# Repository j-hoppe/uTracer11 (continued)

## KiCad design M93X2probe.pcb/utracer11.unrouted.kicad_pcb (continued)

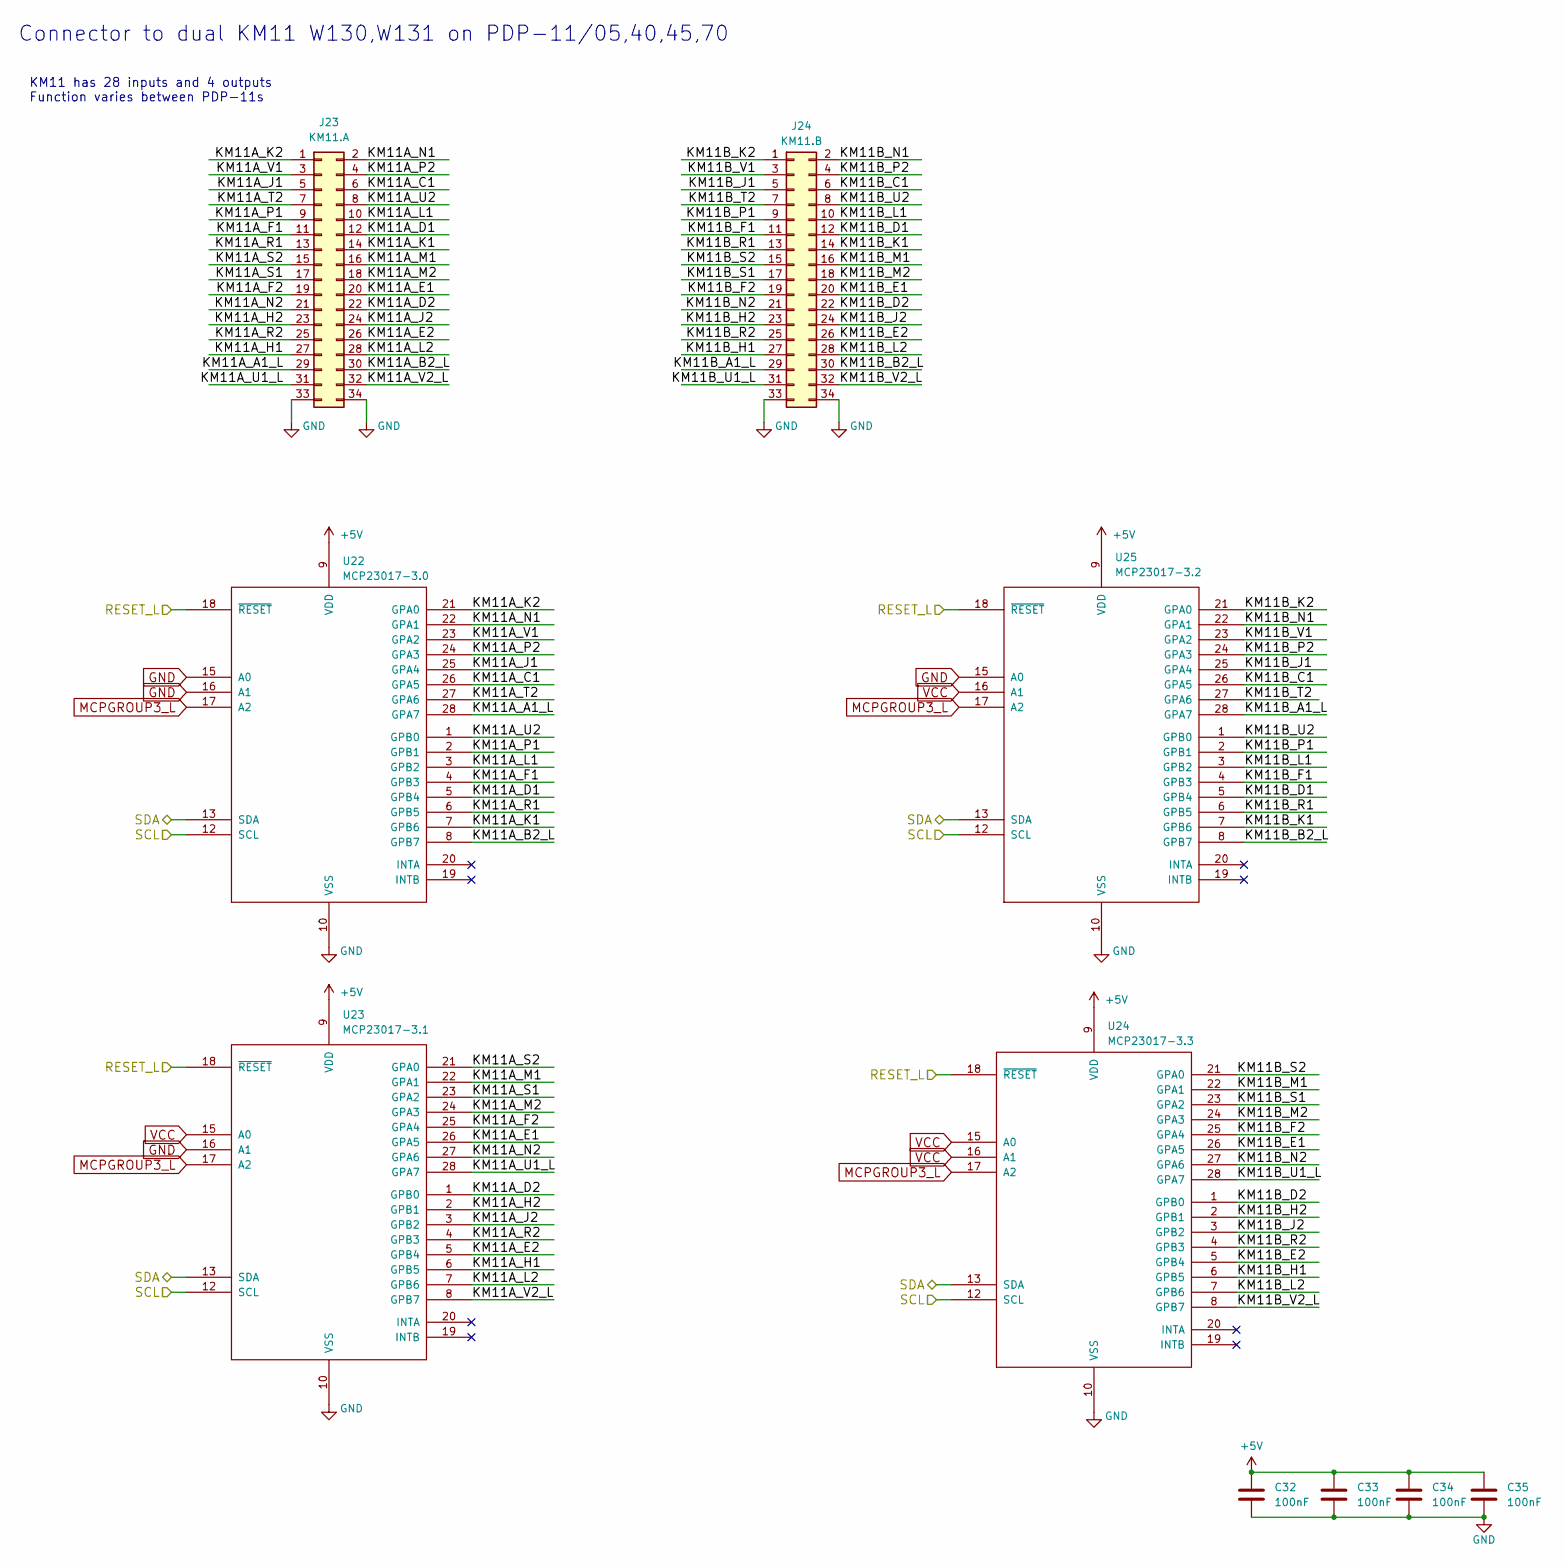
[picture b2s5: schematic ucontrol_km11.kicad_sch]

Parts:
C32, C33, C34, C35: 100nF; C_Disc_D4.3mm_W1.9mm_P5.00mm
J23: KM11.A; IDC-Header_2x17_P2.54mm_Horizontal
J24: KM11.B; IDC-Header_2x17_P2.54mm_Horizontal
U22: MCP23017-3.0; DIP-28_W7.62mm
U23: MCP23017-3.1; DIP-28_W7.62mm
U24: MCP23017-3.3; DIP-28_W7.62mm
U25: MCP23017-3.2; DIP-28_W7.62mm

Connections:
/MCP_RESET_L: U22.18 (~RESET), U23.18 (~RESET), U24.18 (~RESET), U25.18 (~RESET); also elsewhere on the board
/SCL: U22.12 (SCL), U23.12 (SCL), U24.12 (SCL), U25.12 (SCL); also elsewhere on the board
/SDA: U22.13 (SDA), U23.13 (SDA), U24.13 (SDA), U25.13 (SDA); also elsewhere on the board
/ucontrol_km11/KM11A_A1_L: J23.29, U22.28 (GPA7)
/ucontrol_km11/KM11A_B2_L: J23.30, U22.8 (GPB7)
/ucontrol_km11/KM11A_C1: J23.6, U22.26 (GPA5)
/ucontrol_km11/KM11A_D1: J23.12, U22.5 (GPB4)
/ucontrol_km11/KM11A_D2: J23.22, U23.1 (GPB0)
/ucontrol_km11/KM11A_E1: J23.20, U23.26 (GPA5)
/ucontrol_km11/KM11A_E2: J23.26, U23.5 (GPB4)
/ucontrol_km11/KM11A_F1: J23.11, U22.4 (GPB3)
/ucontrol_km11/KM11A_F2: J23.19, U23.25 (GPA4)
/ucontrol_km11/KM11A_H1: J23.27, U23.6 (GPB5)
/ucontrol_km11/KM11A_H2: J23.23, U23.2 (GPB1)
/ucontrol_km11/KM11A_J1: J23.5, U22.25 (GPA4)
/ucontrol_km11/KM11A_J2: J23.24, U23.3 (GPB2)
/ucontrol_km11/KM11A_K1: J23.14, U22.7 (GPB6)
/ucontrol_km11/KM11A_K2: J23.1, U22.21 (GPA0)
/ucontrol_km11/KM11A_L1: J23.10, U22.3 (GPB2)
/ucontrol_km11/KM11A_L2: J23.28, U23.7 (GPB6)
/ucontrol_km11/KM11A_M1: J23.16, U23.22 (GPA1)
/ucontrol_km11/KM11A_M2: J23.18, U23.24 (GPA3)
/ucontrol_km11/KM11A_N1: J23.2, U22.22 (GPA1)
/ucontrol_km11/KM11A_N2: J23.21, U23.27 (GPA6)
/ucontrol_km11/KM11A_P1: J23.9, U22.2 (GPB1)
/ucontrol_km11/KM11A_P2: J23.4, U22.24 (GPA3)
/ucontrol_km11/KM11A_R1: J23.13, U22.6 (GPB5)
/ucontrol_km11/KM11A_R2: J23.25, U23.4 (GPB3)
/ucontrol_km11/KM11A_S1: J23.17, U23.23 (GPA2)
/ucontrol_km11/KM11A_S2: J23.15, U23.21 (GPA0)
/ucontrol_km11/KM11A_T2: J23.7, U22.27 (GPA6)
/ucontrol_km11/KM11A_U1_L: J23.31, U23.28 (GPA7)
/ucontrol_km11/KM11A_U2: J23.8, U22.1 (GPB0)
/ucontrol_km11/KM11A_V1: J23.3, U22.23 (GPA2)
/ucontrol_km11/KM11A_V2_L: J23.32, U23.8 (GPB7)
/ucontrol_km11/KM11B_A1_L: J24.29, U25.28 (GPA7)
/ucontrol_km11/KM11B_B2_L: J24.30, U25.8 (GPB7)
/ucontrol_km11/KM11B_C1: J24.6, U25.26 (GPA5)
/ucontrol_km11/KM11B_D1: J24.12, U25.5 (GPB4)
/ucontrol_km11/KM11B_D2: J24.22, U24.1 (GPB0)
/ucontrol_km11/KM11B_E1: J24.20, U24.26 (GPA5)
/ucontrol_km11/KM11B_E2: J24.26, U24.5 (GPB4)
/ucontrol_km11/KM11B_F1: J24.11, U25.4 (GPB3)
/ucontrol_km11/KM11B_F2: J24.19, U24.25 (GPA4)
/ucontrol_km11/KM11B_H1: J24.27, U24.6 (GPB5)
/ucontrol_km11/KM11B_H2: J24.23, U24.2 (GPB1)
/ucontrol_km11/KM11B_J1: J24.5, U25.25 (GPA4)
/ucontrol_km11/KM11B_J2: J24.24, U24.3 (GPB2)
/ucontrol_km11/KM11B_K1: J24.14, U25.7 (GPB6)
/ucontrol_km11/KM11B_K2: J24.1, U25.21 (GPA0)
/ucontrol_km11/KM11B_L1: J24.10, U25.3 (GPB2)
/ucontrol_km11/KM11B_L2: J24.28, U24.7 (GPB6)
/ucontrol_km11/KM11B_M1: J24.16, U24.22 (GPA1)
/ucontrol_km11/KM11B_M2: J24.18, U24.24 (GPA3)
/ucontrol_km11/KM11B_N1: J24.2, U25.22 (GPA1)
/ucontrol_km11/KM11B_N2: J24.21, U24.27 (GPA6)
/ucontrol_km11/KM11B_P1: J24.9, U25.2 (GPB1)
/ucontrol_km11/KM11B_P2: J24.4, U25.24 (GPA3)
/ucontrol_km11/KM11B_R1: J24.13, U25.6 (GPB5)
/ucontrol_km11/KM11B_R2: J24.25, U24.4 (GPB3)
/ucontrol_km11/KM11B_S1: J24.17, U24.23 (GPA2)
/ucontrol_km11/KM11B_S2: J24.15, U24.21 (GPA0)
/ucontrol_km11/KM11B_T2: J24.7, U25.27 (GPA6)
/ucontrol_km11/KM11B_U1_L: J24.31, U24.28 (GPA7)
/ucontrol_km11/KM11B_U2: J24.8, U25.1 (GPB0)
/ucontrol_km11/KM11B_V1: J24.3, U25.23 (GPA2)
/ucontrol_km11/KM11B_V2_L: J24.32, U24.8 (GPB7)
GND: C32.2, C33.2, C34.2, C35.2, J23.33, J23.34, J24.33, J24.34, U22.10 (VSS), U22.15 (A0), U22.16 (A1), U23.10 (VSS), U23.16 (A1), U24.10 (VSS), U25.10 (VSS), U25.15 (A0); also elsewhere on the board
MCPGROUP3_L: U22.17 (A2), U23.17 (A2), U24.17 (A2), U25.17 (A2); also elsewhere on the board
UB_5V: C32.1, C33.1, C34.1, C35.1, U22.9 (VDD), U23.9 (VDD), U23.15 (A0), U24.9 (VDD), U24.15 (A0), U24.16 (A1), U25.9 (VDD), U25.16 (A1); also elsewhere on the board

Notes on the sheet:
Connector to dual KM11 W130,W131 on PDP-11/05,40,45,70
KM11 has 28 inputs and 4 outputs Function varies between PDP-11s

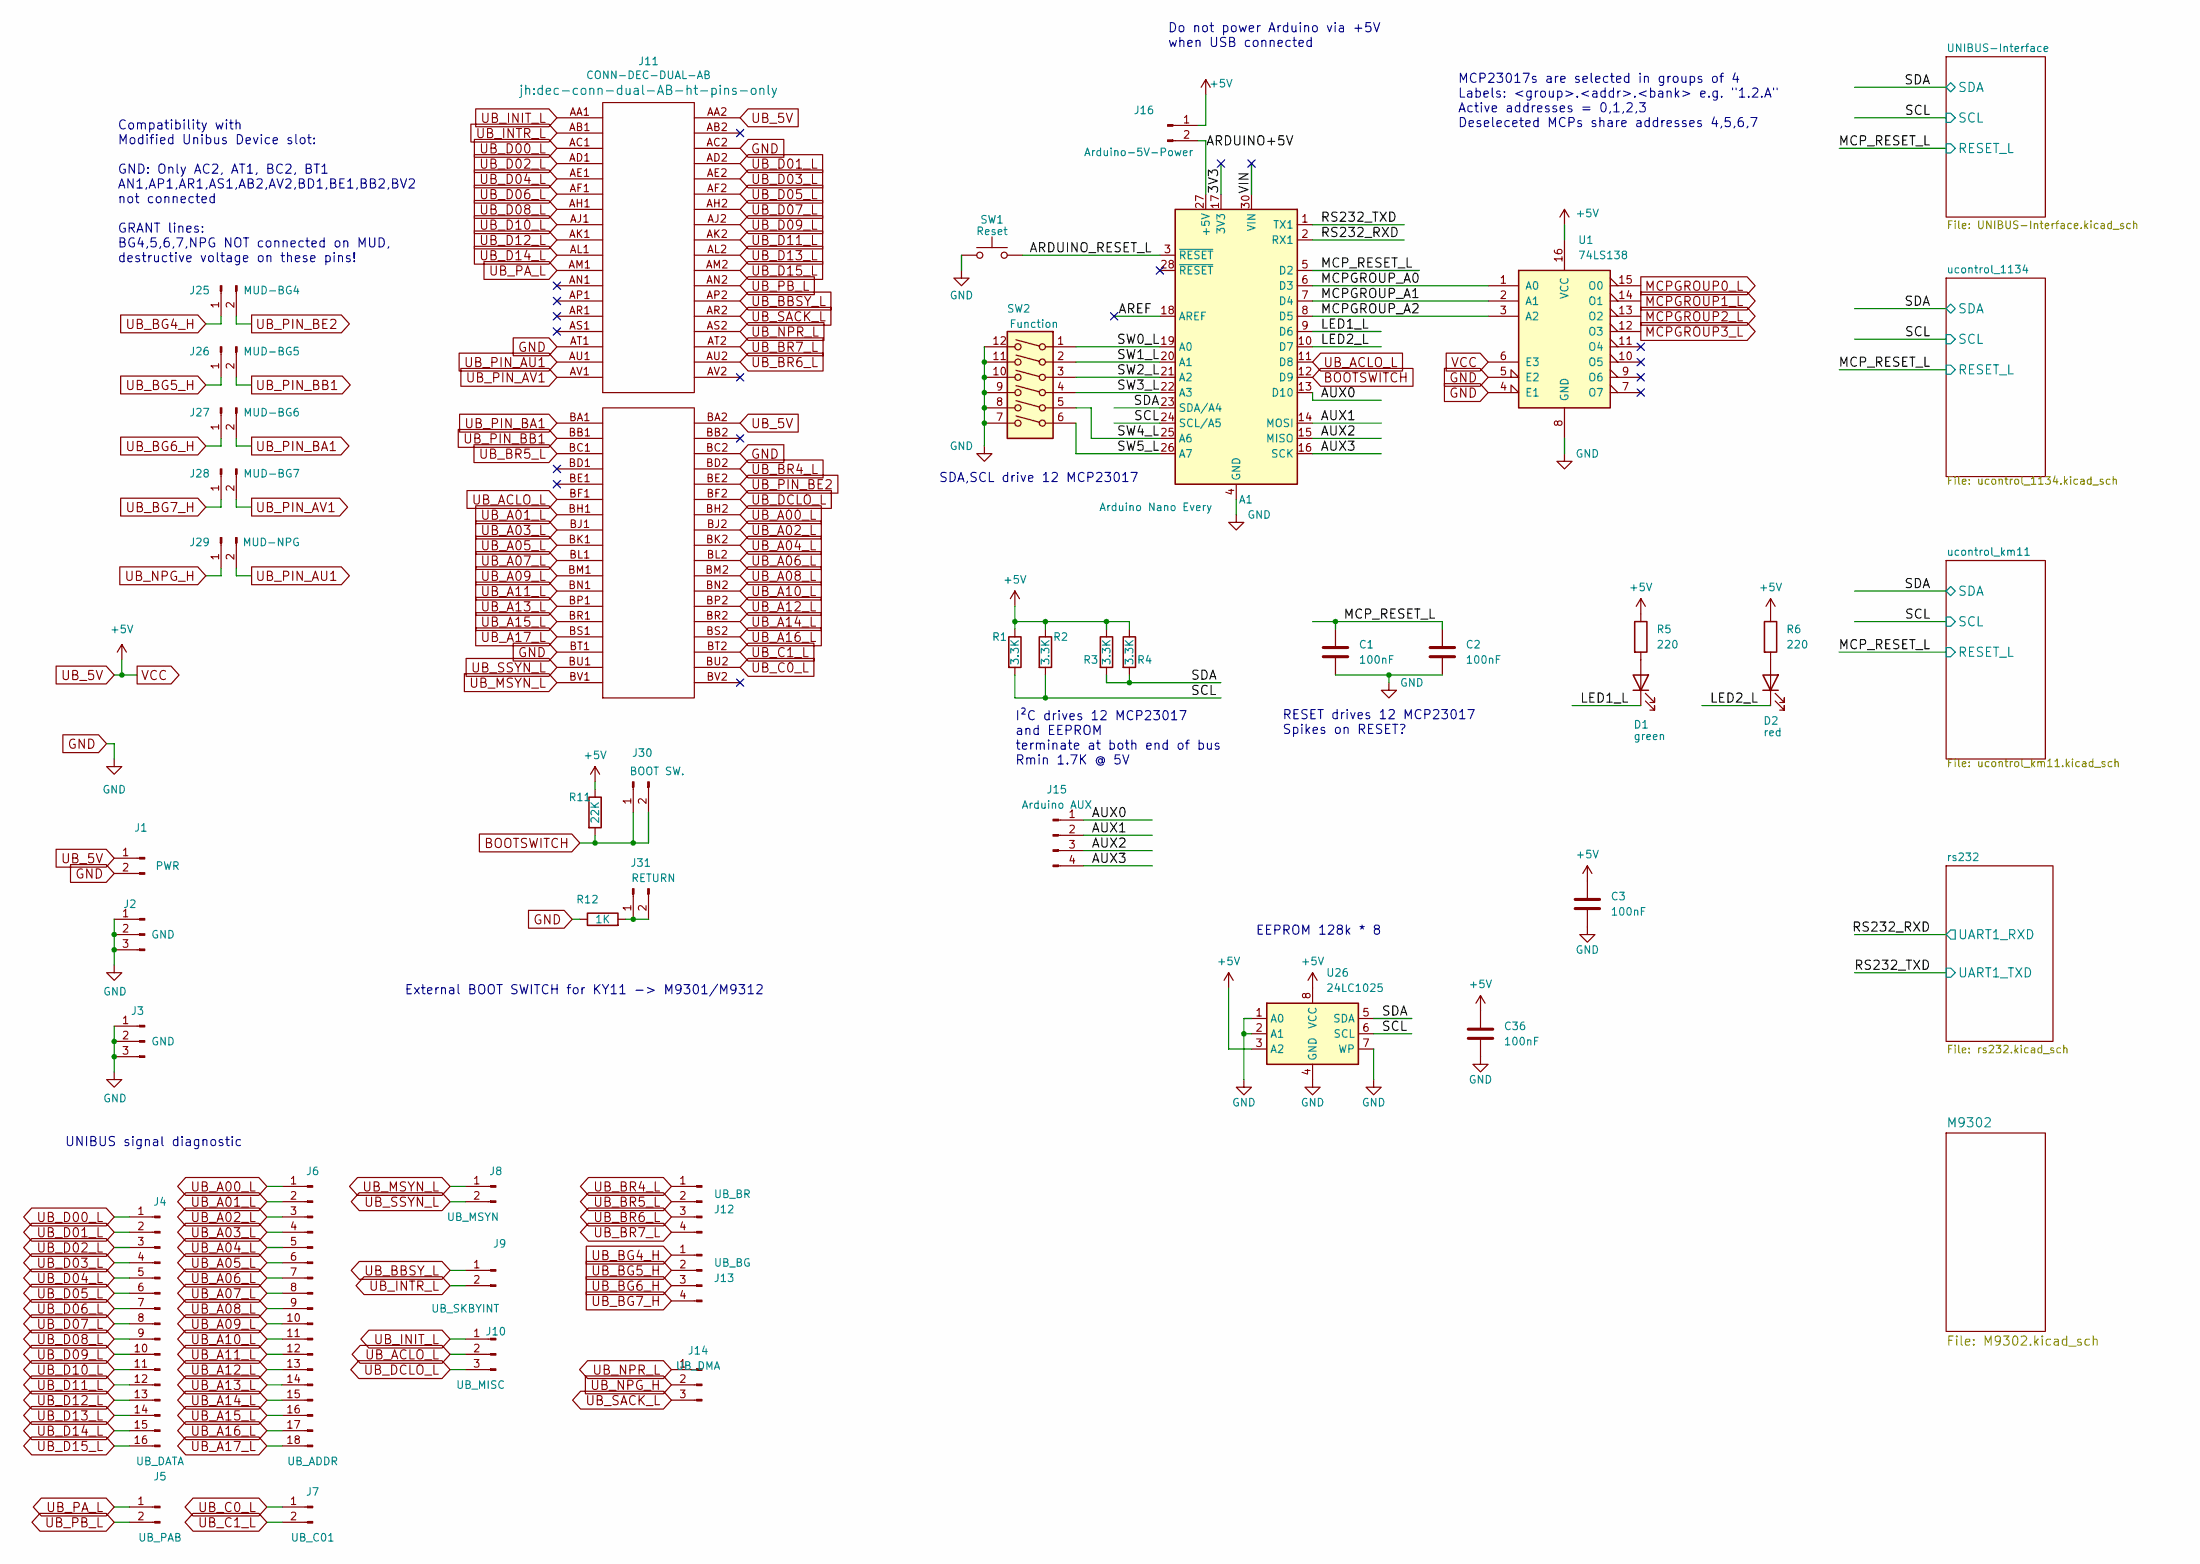
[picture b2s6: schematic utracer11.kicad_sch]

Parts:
A1: Arduino Nano Every; Arduino_Nano
C1, C2, C3, C36: 100nF; C_Disc_D4.3mm_W1.9mm_P5.00mm
D1: green; LED_D3.0mm_Horizontal_O3.81mm_Z2.0mm
D2: red; LED_D3.0mm_Horizontal_O3.81mm_Z2.0mm
J1: PWR; PinHeader_1x02_P2.54mm_Vertical
J2, J3: GND; PinHeader_1x03_P2.54mm_Vertical
J4: UB_DATA; PinHeader_1x16_P2.54mm_Vertical
J5: UB_PAB; PinHeader_1x02_P2.54mm_Vertical
J6: UB_ADDR; PinHeader_1x18_P2.54mm_Vertical
J7: UB_C01; PinHeader_1x02_P2.54mm_Vertical
J8: UB_MSYN; PinHeader_1x02_P2.54mm_Vertical
J9: UB_SKBYINT; PinHeader_1x02_P2.54mm_Vertical
J10: UB_MISC; PinHeader_1x03_P2.54mm_Vertical
J11: CONN-DEC-DUAL-AB; dec-conn-dual-AB-ht-pins-only
J12: UB_BR; PinHeader_1x04_P2.54mm_Vertical
J13: UB_BG; PinHeader_1x04_P2.54mm_Vertical
J14: UB_DMA; PinHeader_1x03_P2.54mm_Vertical
J15: Arduino AUX; PinHeader_1x04_P2.54mm_Vertical
J16: Arduino-5V-Power; PinHeader_1x02_P2.54mm_Vertical
J25: MUD-BG4; PinHeader_1x02_P2.54mm_Vertical
J26: MUD-BG5; PinHeader_1x02_P2.54mm_Vertical
J27: MUD-BG6; PinHeader_1x02_P2.54mm_Vertical
J28: MUD-BG7; PinHeader_1x02_P2.54mm_Vertical
J29: MUD-NPG; PinHeader_1x02_P2.54mm_Vertical
J30: BOOT SW.; SolderWirePad_1x02_P5.08mm_Drill1.5mm
J31: RETURN; SolderWirePad_1x02_P5.08mm_Drill1.5mm
R1, R2, R3, R4: 3.3K; R_Axial_DIN0207_L6.3mm_D2.5mm_P2.54mm_Vertical; LCSC C26010
R5, R6: 220; R_Axial_DIN0207_L6.3mm_D2.5mm_P2.54mm_Vertical
R11: 22K; R_Axial_DIN0207_L6.3mm_D2.5mm_P7.62mm_Horizontal; LCSC C26010
R12: 1K; R_Axial_DIN0207_L6.3mm_D2.5mm_P7.62mm_Horizontal; LCSC C26010
SW1: Reset; SW_Tactile_SPST_Angled_PTS645Vx58-2LFS
SW2: Function; SW_DIP_SPSTx06_Piano_CTS_Series194-6MSTN_W7.62mm_P2.54mm
U1: 74LS138; DIP-16_W7.62mm
U26: 24LC1025; DIP-8_W7.62mm

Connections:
/3V3: A1.17 (3V3)
/ARDUINO+5V: A1.27 (+5V), J16.2
/ARDUINO_RESET_L: A1.3 (~RESET), SW1.2
/AREF: A1.18 (AREF)
/AUX0: A1.13 (D10), J15.1
/AUX1: A1.14 (MOSI), J15.2
/AUX2: A1.15 (MISO), J15.3
/AUX3: A1.16 (SCK), J15.4
/LED1_L: A1.9 (D6), D1.1 (K)
/LED2_L: A1.10 (D7), D2.1 (K)
/MCPGROUP_A0: A1.6 (D3), U1.1 (A0)
/MCPGROUP_A1: A1.7 (D4), U1.2 (A1)
/MCPGROUP_A2: A1.8 (D5), U1.3 (A2)
/MCP_RESET_L: A1.5 (D2), C1.1, C2.1; also elsewhere on the board
/RS232_RXD: A1.2 (RX1); also elsewhere on the board
/RS232_TXD: A1.1 (TX1); also elsewhere on the board
/SCL: A1.24 (SCL/A5), R1.2, R2.2, U26.6 (SCL); also elsewhere on the board
/SDA: A1.23 (SDA/A4), R3.2, R4.2, U26.5 (SDA); also elsewhere on the board
/SW0_L: A1.19 (A0), SW2.1
/SW1_L: A1.20 (A1), SW2.2
/SW2_L: A1.21 (A2), SW2.3
/SW3_L: A1.22 (A3), SW2.4
/SW4_L: A1.25 (A6), SW2.5
/SW5_L: A1.26 (A7), SW2.6
/VIN: A1.30 (VIN)
BOOTSWITCH: A1.12 (D9), J30.1, J30.2, R11.2
GND: A1.4 (GND), A1.29 (GND), C1.2, C2.2, C3.2, C36.2, J1.2, J2.1, J2.2, J2.3, J3.1, J3.2, J3.3, J11.AC2, J11.AT1, J11.BC2, J11.BT1, R12.1, SW1.1, SW2.7, SW2.8, SW2.9, SW2.10, SW2.11, SW2.12, U1.4 (E1), U1.5 (E2), U1.8 (GND), U26.1 (A0), U26.2 (A1), U26.4 (GND), U26.7 (WP); also elsewhere on the board
MCPGROUP0_L: U1.15 (O0); also elsewhere on the board
MCPGROUP1_L: U1.14 (O1); also elsewhere on the board
MCPGROUP2_L: U1.13 (O2); also elsewhere on the board
MCPGROUP3_L: U1.12 (O3); also elsewhere on the board
unnamed: D1.2 (A), R5.2
unnamed: D2.2 (A), R6.2
unnamed: J31.1, J31.2, R12.2
UB_5V: C3.1, C36.1, J1.1, J11.AA2, J11.BA2, J16.1, R1.1, R2.1, R3.1, R4.1, R5.1, R6.1, R11.1, U1.6 (E3), U1.16 (VCC), U26.3 (A2), U26.8 (VCC); also elsewhere on the board
UB_A00_L: J6.1, J11.BH2; also elsewhere on the board
UB_A01_L: J6.2, J11.BH1; also elsewhere on the board
UB_A02_L: J6.3, J11.BJ2; also elsewhere on the board
UB_A03_L: J6.4, J11.BJ1; also elsewhere on the board
UB_A04_L: J6.5, J11.BK2; also elsewhere on the board
UB_A05_L: J6.6, J11.BK1; also elsewhere on the board
UB_A06_L: J6.7, J11.BL2; also elsewhere on the board
UB_A07_L: J6.8, J11.BL1; also elsewhere on the board
UB_A08_L: J6.9, J11.BM2; also elsewhere on the board
UB_A09_L: J6.10, J11.BM1; also elsewhere on the board
UB_A10_L: J6.11, J11.BN2; also elsewhere on the board
UB_A11_L: J6.12, J11.BN1; also elsewhere on the board
UB_A12_L: J6.13, J11.BP2; also elsewhere on the board
UB_A13_L: J6.14, J11.BP1; also elsewhere on the board
UB_A14_L: J6.15, J11.BR2; also elsewhere on the board
UB_A15_L: J6.16, J11.BR1; also elsewhere on the board
UB_A16_L: J6.17, J11.BS2; also elsewhere on the board
UB_A17_L: J6.18, J11.BS1; also elsewhere on the board
UB_ACLO_L: A1.11 (D8), J10.2, J11.BF1; also elsewhere on the board
UB_BBSY_L: J9.1, J11.AP2; also elsewhere on the board
UB_BG4_H: J13.1, J25.1; also elsewhere on the board
UB_BG5_H: J13.2, J26.1; also elsewhere on the board
UB_BG6_H: J13.3, J27.1; also elsewhere on the board
UB_BG7_H: J13.4, J28.1; also elsewhere on the board
UB_BR4_L: J11.BD2, J12.1; also elsewhere on the board
UB_BR5_L: J11.BC1, J12.2; also elsewhere on the board
UB_BR6_L: J11.AU2, J12.3; also elsewhere on the board
UB_BR7_L: J11.AT2, J12.4; also elsewhere on the board
UB_C0_L: J7.1, J11.BU2; also elsewhere on the board
UB_C1_L: J7.2, J11.BT2; also elsewhere on the board
UB_D00_L: J4.1, J11.AC1; also elsewhere on the board
UB_D01_L: J4.2, J11.AD2; also elsewhere on the board
UB_D02_L: J4.3, J11.AD1; also elsewhere on the board
UB_D03_L: J4.4, J11.AE2; also elsewhere on the board
UB_D04_L: J4.5, J11.AE1; also elsewhere on the board
UB_D05_L: J4.6, J11.AF2; also elsewhere on the board
UB_D06_L: J4.7, J11.AF1; also elsewhere on the board
UB_D07_L: J4.8, J11.AH2; also elsewhere on the board
UB_D08_L: J4.9, J11.AH1; also elsewhere on the board
UB_D09_L: J4.10, J11.AJ2; also elsewhere on the board
UB_D10_L: J4.11, J11.AJ1; also elsewhere on the board
UB_D11_L: J4.12, J11.AK2; also elsewhere on the board
UB_D12_L: J4.13, J11.AK1; also elsewhere on the board
UB_D13_L: J4.14, J11.AL2; also elsewhere on the board
UB_D14_L: J4.15, J11.AL1; also elsewhere on the board
UB_D15_L: J4.16, J11.AM2; also elsewhere on the board
UB_DCLO_L: J10.3, J11.BF2; also elsewhere on the board
UB_INIT_L: J10.1, J11.AA1; also elsewhere on the board
UB_INTR_L: J9.2, J11.AB1; also elsewhere on the board
UB_MSYN_L: J8.1, J11.BV1; also elsewhere on the board
UB_NPG_H: J14.2, J29.1; also elsewhere on the board
UB_NPR_L: J11.AS2, J14.1; also elsewhere on the board
UB_PA_L: J5.1, J11.AM1; also elsewhere on the board
UB_PB_L: J5.2, J11.AN2; also elsewhere on the board
UB_PIN_AU1: J11.AU1, J29.2
UB_PIN_AV1: J11.AV1, J28.2
UB_PIN_BA1: J11.BA1, J27.2
UB_PIN_BB1: J11.BB1, J26.2
UB_PIN_BE2: J11.BE2, J25.2
UB_SACK_L: J11.AR2, J14.3; also elsewhere on the board
UB_SSYN_L: J8.2, J11.BU1; also elsewhere on the board

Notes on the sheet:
Do not power Arduino via +5V when USB connected
Compatibility with Modified Unibus Device slot: GND: Only AC2, AT1, BC2, BT1 AN1,AP1,AR1,AS1,AB2,AV2,BD1,BE1,BB2,BV2 not connected GRANT lines: BG4,5,6,7,NPG NOT connected on MUD, destructive voltage on these pins!
External BOOT SWITCH for KY11 -> M9301/M9312
MCP23017s are selected in groups of 4 Labels: <group>.<addr>.<bank> e.g. "1.2.A" Active addresses = 0,1,2,3 Deseleceted MCPs share addresses 4,5,6,7
UNIBUS signal diagnostic
I²C drives 12 MCP23017 and EEPROM terminate at both end of bus Rmin 1.7K @ 5V
RESET drives 12 MCP23017 Spikes on RESET?
EEPROM 128k * 8
SDA,SCL drive 12 MCP23017

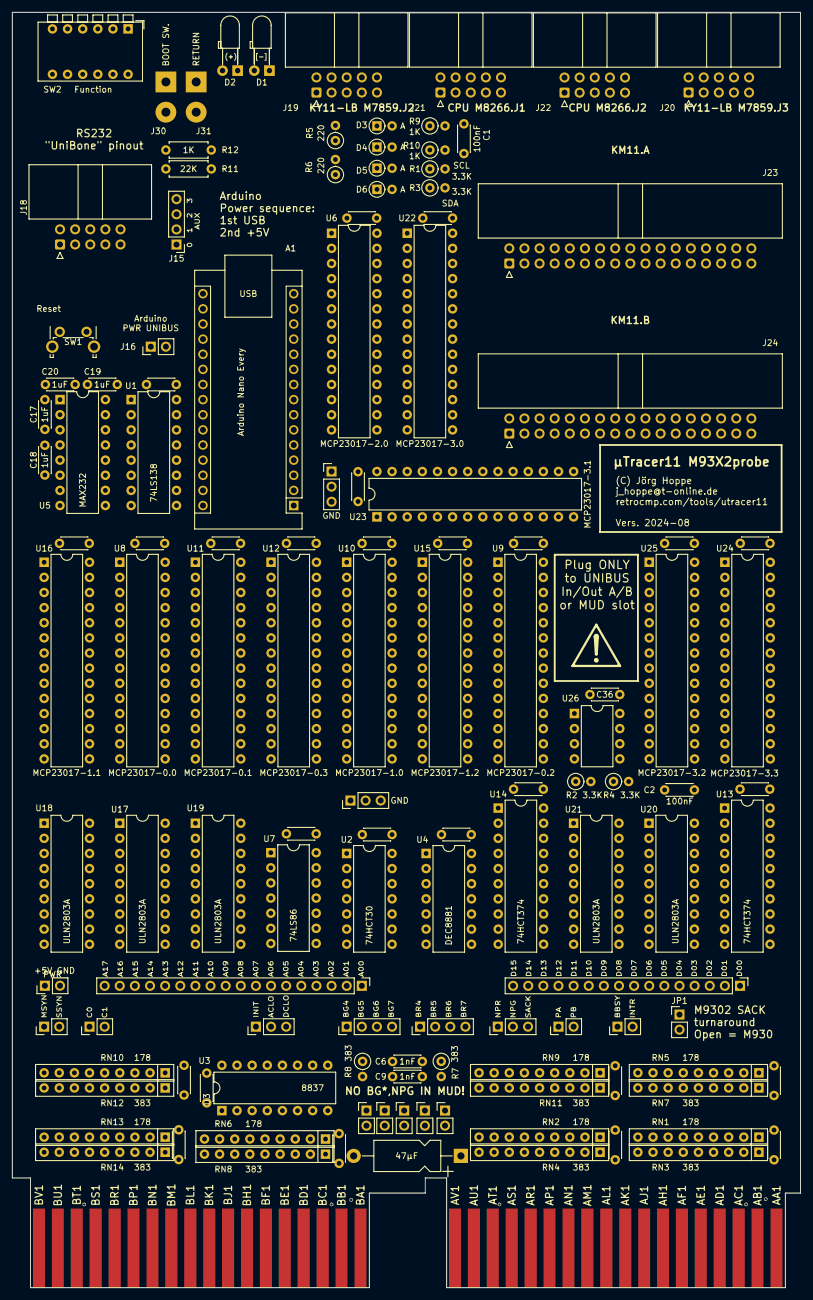
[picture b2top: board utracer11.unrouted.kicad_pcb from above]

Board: 4 copper layers, 132.3 x 214.1 mm, 128 parts (0 on the bottom side), 253 nets.

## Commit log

2024-09-06 initial
2024-09-14 Simulator console window
2024-09-14 typo
2024-09-15 exclude common/simulator from gui build
2024-09-24 label indicating state of micromachine, F10 "fullscreen" hotkey
2024-09-25 micro clock enable/disable via KY11LB ok
2024-09-25 11/34micro clock enable/disable via KY11LB ok
2024-09-28 code format
2024-09-28 cloned from pdp1134sim
2024-09-28 refactored pdp1140km11state, KM11 signals connected to simulator
2024-09-29 pdp1140sim clock enable and single step ok
2024-10-10 GUI states, auto stepping
2024-10-12 autostepping, compiles
2024-10-13 Linux compile ok
2024-10-14 Simulators: Work on connection logic, sending of unibus cycles only when umachine stopped
2024-10-14 Autostepping GUI and logic
2024-10-14 Autostepping brakes at MPC and UNIBUS fetch
2024-10-15 TraceController grid with extra empty row to compensate scroll problems
2024-10-15 tracegrid as CSV to clipboard
2024-10-16 microword panel, static
2024-10-20 singel exaM: update data field
2024-10-20 upodate pdp1140sim to 1134 state
2024-10-25 PDP11/34 micro store from ROM readouts
2024-10-25 Unified naming
2024-10-25 more comments
2024-10-26 binary helper
2024-10-26 burn in
2024-10-26 start display dynamic micro store
2024-10-27 ucontrol store xml and parser compiles
2024-10-27 rendering text annotations compile
2024-10-27 refactoring annotions,geometry proerties
2024-10-27 uword dispaly showing bits now
2024-10-27 refactoring: "uword" -> "controlword" 11/34 control word fields
2024-10-27 renamed from history.txt
2024-10-27 pdp11/34 control store fields definition
2024-10-28 11/control world bits shown the first time
2024-10-28 controlword bit display logic
2024-10-28 control word display highlights labels and table entries
2024-10-28 cleanup gcc -Wall -Wextra
2024-10-28 remove <label> tags
2024-10-28 fine tuning bit positions
2024-11-09 fiddled with PDP11/40 KM11 wires and logic levels
2024-11-10 Fix of KM11 wiring out01 <-> out10
2024-11-11 fix polarity of mclk and mclk_enab on write
2024-11-14 fix startup logic for 1140
2024-11-18 ^repalce synthetic KM11 signals "Inxx, out**" with flipchip pin names
2024-11-20 Windows resize back from fullscreen F10
2024-11-20 remove in**, out** silk, change to flipchip signals K2,P1,...
2024-11-20 pdp1140 simualotr sent double and wrong mpc, separeted 11/40 KM11 into KM11A and KM11B
2025-01-01 telnet compatible
2025-01-01 typos
2025-01-01 Fix for Linux
2025-01-01 New class "Variable" and "VariableMap", used for MessagesStateDef and ...Value
2025-01-05 fix reichelt partnumbers
2025-01-07 introduced uniform "stateVar" list, logic to display state changes in "trace" window
2025-01-09 part update
2025-01-16 change in diag fprintf()
2025-01-17 begin ECMA script
2025-01-17 script intergrated, log() function ok
2025-01-20 error
2025-01-27 Big change: Scripting. Enhanced message flow (tags, function renaming), trace window (statevar change display)
2025-01-27 trace window: unibus cycles recveived correctly
2025-01-27 cleanup
2025-01-28 keep latest request/response tag
2025-01-28 Message tag: uint16_t -> enum MsgTag
2025-01-30 script tests
2025-01-31 scripting with selective test for state vars OK
2025-02-01 clearing trace in activity caused assertion
2025-02-08 coded Eeprom messages and low level read/write logic, now testable
2025-02-09 eeprom read&write ok
2025-02-14 eeprom read/write with variable number of bytes
2025-02-14 disable logging
2025-02-17 starting M93X2 eeprom file system
2025-03-15 make eeprom filesystem compilable
